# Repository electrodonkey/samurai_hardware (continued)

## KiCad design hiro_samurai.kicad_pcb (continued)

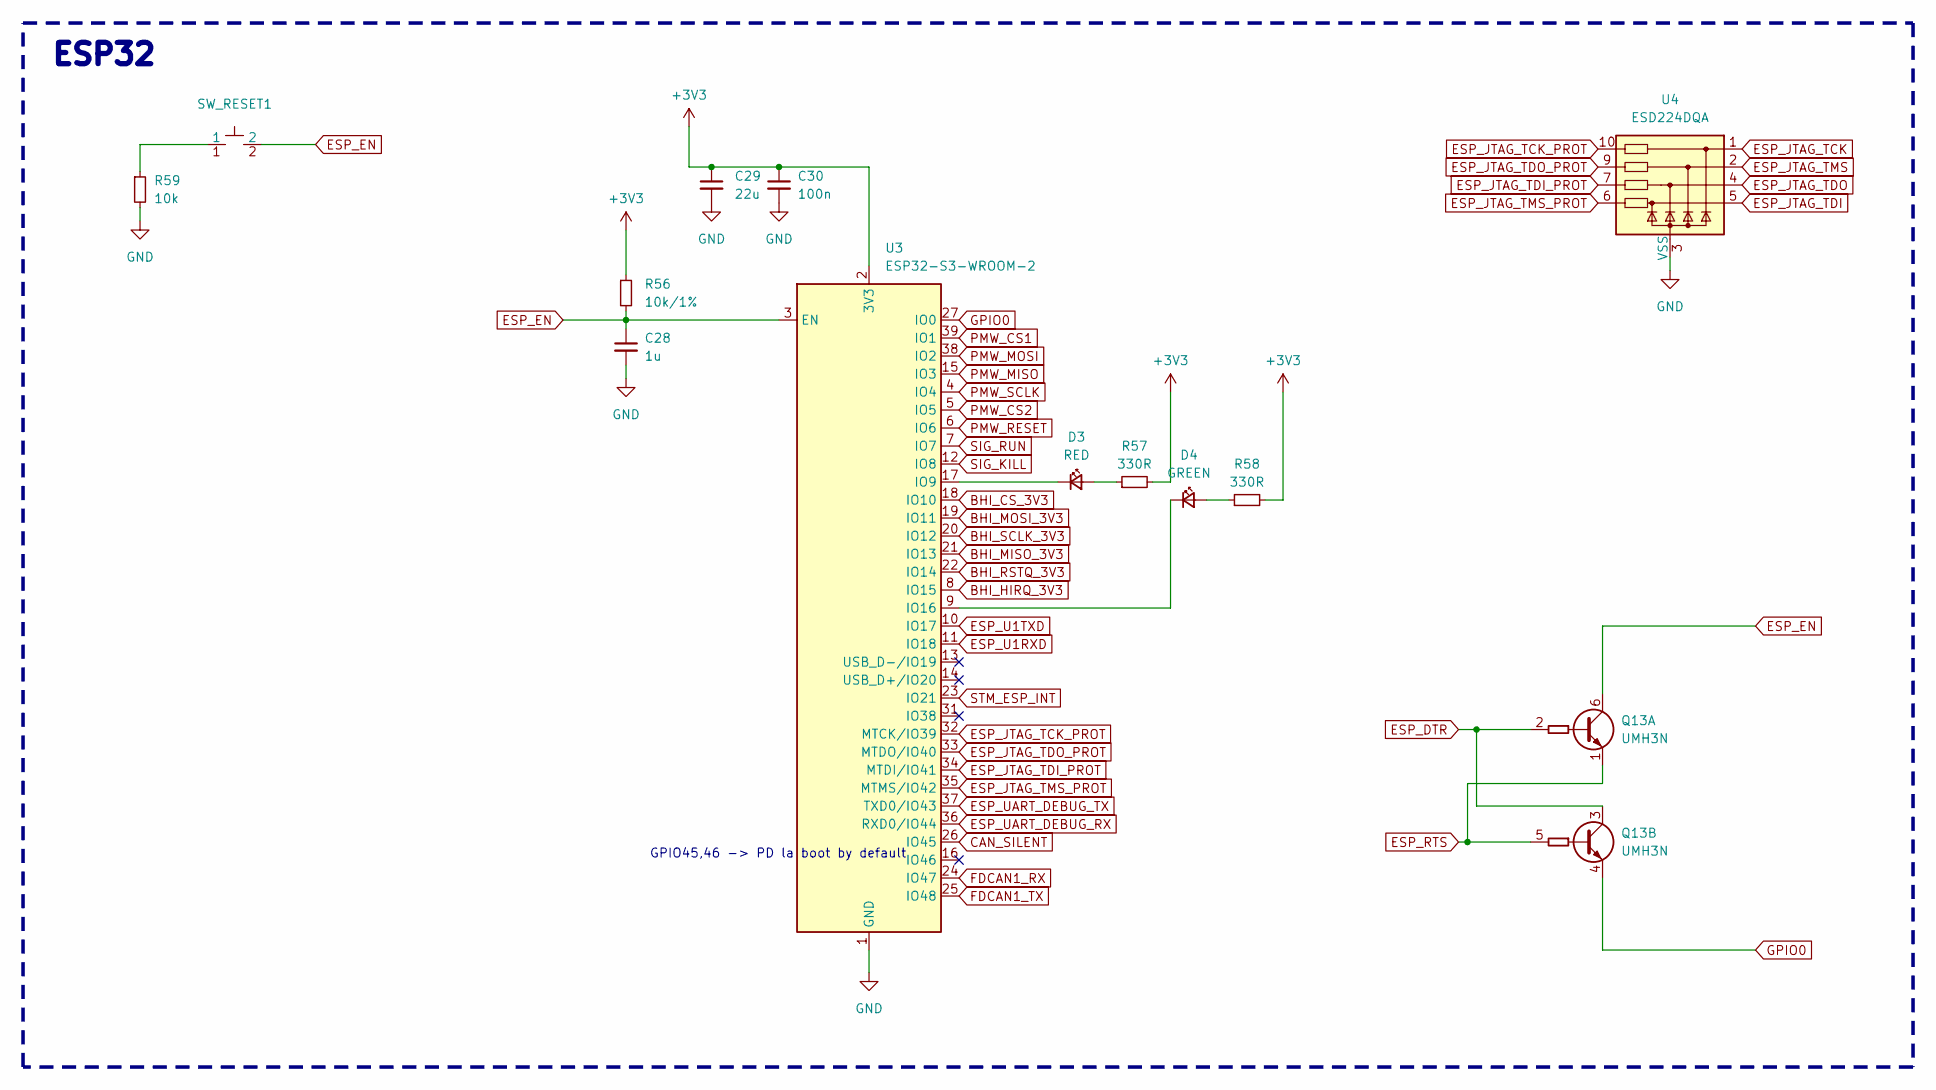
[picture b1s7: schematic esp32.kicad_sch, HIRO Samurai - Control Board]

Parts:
C28: 1u; C_0402_1005Metric_Pad0.74x0.62mm_HandSolder
C29: 22u; C_0603_1608Metric_Pad1.08x0.95mm_HandSolder
C30: 100n; C_0402_1005Metric_Pad0.74x0.62mm_HandSolder
D3: RED; LED_0603_1608Metric_Pad1.05x0.95mm_HandSolder
D4: GREEN; LED_0603_1608Metric_Pad1.05x0.95mm_HandSolder
Q13: UMH3N; SOT-363_SC-70-6
R56: 10k/1%; R_0402_1005Metric_Pad0.72x0.64mm_HandSolder
R57, R58: 330R; R_0402_1005Metric_Pad0.72x0.64mm_HandSolder
R59: 10k; R_0402_1005Metric_Pad0.72x0.64mm_HandSolder
SW_RESET1: TL1017AABF160QG
U3: ESP32-S3-WROOM-2
U4: ESD224DQA; Diodes_UDFN-10_1.0x2.5mm_P0.5mm

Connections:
+3V3: C29.1, C30.1, R56.1, R57.2, R58.2, U3.2 (3V3); also elsewhere on the board
BHI_CS_3V3: U3.18 (IO10); also elsewhere on the board
BHI_HIRQ_3V3: U3.8 (IO15); also elsewhere on the board
BHI_MISO_3V3: U3.21 (IO13); also elsewhere on the board
BHI_MOSI_3V3: U3.19 (IO11); also elsewhere on the board
BHI_RSTQ_3V3: U3.22 (IO14); also elsewhere on the board
BHI_SCLK_3V3: U3.20 (IO12); also elsewhere on the board
CAN_SILENT: U3.26 (IO45); also elsewhere on the board
ESP_DTR: Q13.2 (B1), Q13.3 (C2); also elsewhere on the board
ESP_EN: C28.1, Q13.6 (C1), R56.2, SW_RESET1.2, U3.3 (EN); also elsewhere on the board
ESP_JTAG_TCK: U4.1; also elsewhere on the board
ESP_JTAG_TCK_PROT: U3.32 (MTCK/IO39), U4.10
ESP_JTAG_TDI: U4.5; also elsewhere on the board
ESP_JTAG_TDI_PROT: U3.34 (MTDI/IO41), U4.7
ESP_JTAG_TDO: U4.4; also elsewhere on the board
ESP_JTAG_TDO_PROT: U3.33 (MTDO/IO40), U4.9
ESP_JTAG_TMS: U4.2; also elsewhere on the board
ESP_JTAG_TMS_PROT: U3.35 (MTMS/IO42), U4.6
ESP_RTS: Q13.1 (E1), Q13.5 (B2); also elsewhere on the board
ESP_U1RXD: U3.11 (IO18); also elsewhere on the board
ESP_U1TXD: U3.10 (IO17); also elsewhere on the board
ESP_UART_DEBUG_RX: U3.36 (RXD0/IO44); also elsewhere on the board
ESP_UART_DEBUG_TX: U3.37 (TXD0/IO43); also elsewhere on the board
FDCAN1_RX: U3.24 (IO47); also elsewhere on the board
FDCAN1_TX: U3.25 (IO48); also elsewhere on the board
GND: C28.2, C29.2, C30.2, R59.2, U3.1 (GND), U3.40 (GND), U3.41 (GND), U4.3 (VSS), U4.8 (VSS); also elsewhere on the board
GPIO0: Q13.4 (E2), U3.27 (IO0)
unnamed: D3.2 (A), R57.1
unnamed: D3.1 (K), U3.17 (IO9)
unnamed: D4.2 (A), R58.1
unnamed: D4.1 (K), U3.9 (IO16)
unnamed: R59.1, SW_RESET1.1
PMW_CS1: U3.39 (IO1); also elsewhere on the board
PMW_CS2: U3.5 (IO5); also elsewhere on the board
PMW_MISO: U3.15 (IO3); also elsewhere on the board
PMW_MOSI: U3.38 (IO2); also elsewhere on the board
PMW_RESET: U3.6 (IO6); also elsewhere on the board
PMW_SCLK: U3.4 (IO4); also elsewhere on the board
SIG_KILL: U3.12 (IO8); also elsewhere on the board
SIG_RUN: U3.7 (IO7); also elsewhere on the board
STM_ESP_INT: U3.23 (IO21); also elsewhere on the board

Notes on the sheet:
GPIO45,46 -> PD la boot by default
ESP32

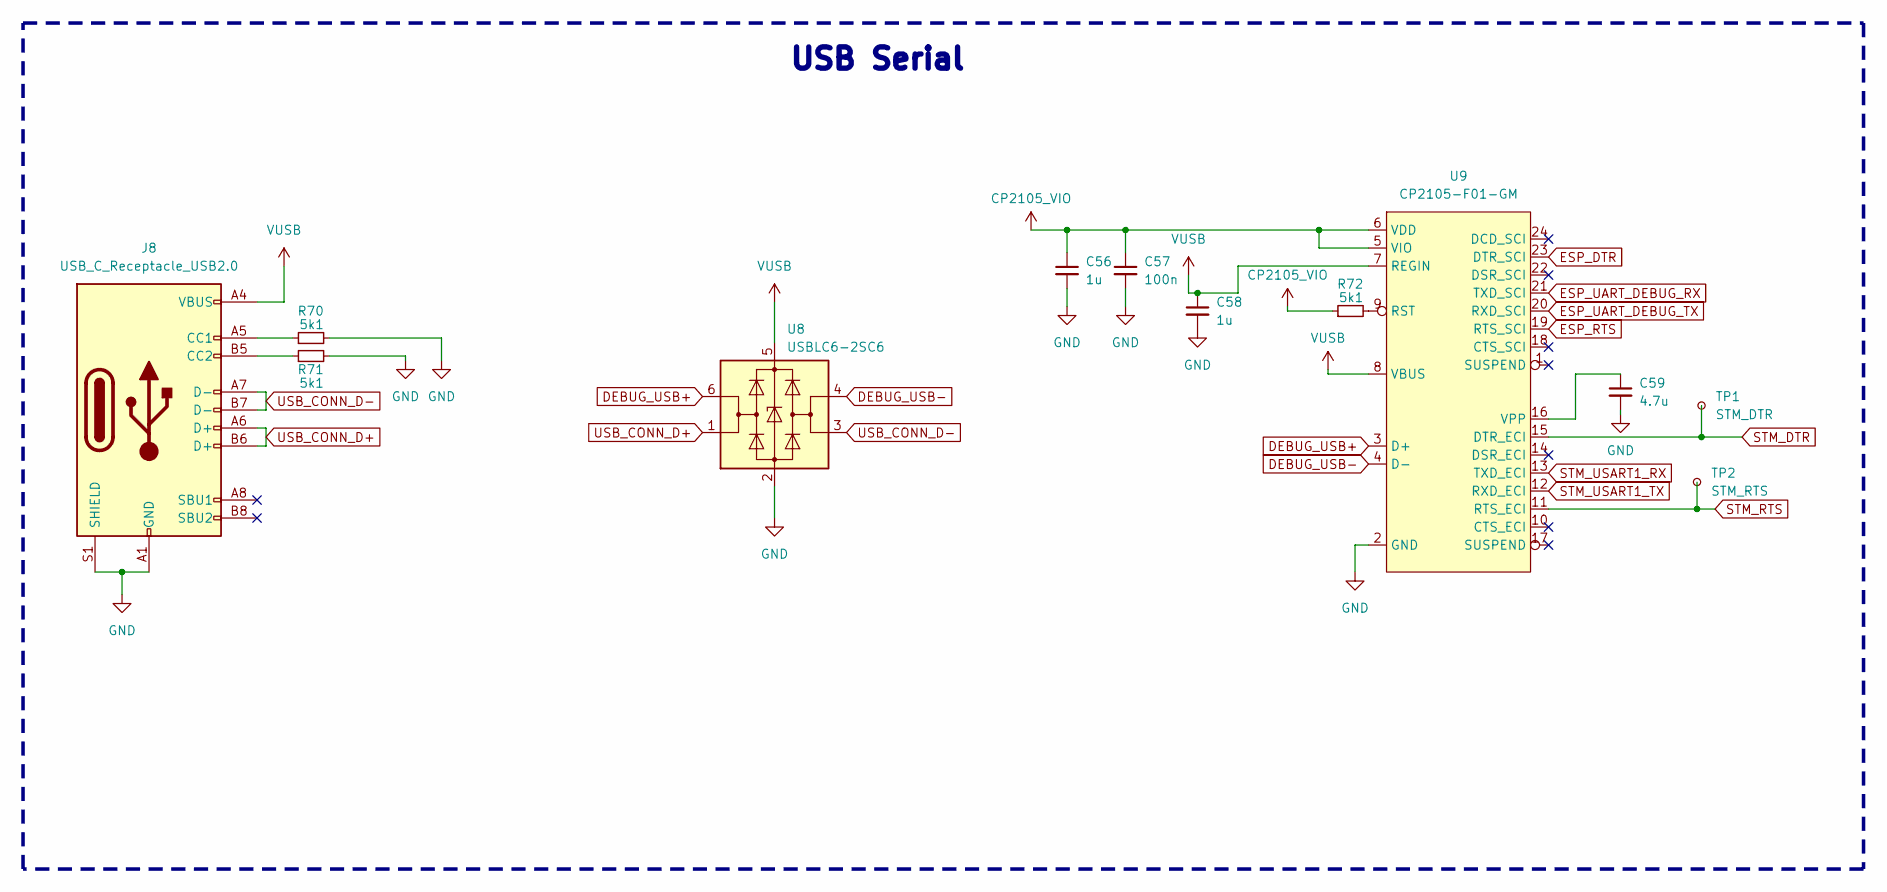
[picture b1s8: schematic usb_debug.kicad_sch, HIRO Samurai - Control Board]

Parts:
C56, C58: 1u; C_0402_1005Metric_Pad0.74x0.62mm_HandSolder
C57: 100n; C_0402_1005Metric_Pad0.74x0.62mm_HandSolder
C59: 4.7u; C_0402_1005Metric_Pad0.74x0.62mm_HandSolder
J8: USB_C_Receptacle_USB2.0; USB_C_Receptacle_GCT_USB4115-03-C
R70, R71, R72: 5k1; R_0402_1005Metric_Pad0.72x0.64mm_HandSolder
TP1: STM_DTR; TestPoint_Pad_D1.0mm
TP2: STM_RTS; TestPoint_Pad_D1.0mm
U8: USBLC6-2SC6; SOT-23-6
U9: CP2105-F01-GM; QFN-24-1EP_4x4mm_P0.5mm_EP2.7x2.7mm

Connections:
CP2105_VIO: C56.1, C57.1, R72.1, U9.5 (VIO), U9.6 (VDD)
DEBUG_USB+: U8.6 (I/O1), U9.3 (D+)
DEBUG_USB-: U8.4 (I/O2), U9.4 (D-)
ESP_DTR: U9.23 (DTR_SCI); also elsewhere on the board
ESP_RTS: U9.19 (RTS_SCI); also elsewhere on the board
ESP_UART_DEBUG_RX: U9.21 (TXD_SCI); also elsewhere on the board
ESP_UART_DEBUG_TX: U9.20 (RXD_SCI); also elsewhere on the board
GND: C56.2, C57.2, C58.2, C59.2, J8.A1 (GND), J8.A12 (GND), J8.B1 (GND), J8.B12 (GND), J8.S1 (SHIELD), R70.2, R71.2, U8.2 (GND), U9.2 (GND); also elsewhere on the board
unnamed: J8.A5 (CC1), R70.1
unnamed: J8.B5 (CC2), R71.1
unnamed: R72.2, U9.9 (RST)
unnamed: C59.1, U9.16 (VPP)
STM_DTR: TP1.1, U9.15 (DTR_ECI)
STM_RTS: TP2.1, U9.11 (RTS_ECI)
STM_USART1_RX: U9.13 (TXD_ECI); also elsewhere on the board
STM_USART1_TX: U9.12 (RXD_ECI); also elsewhere on the board
USB_CONN_D+: J8.A6 (D+), J8.B6 (D+), U8.1 (I/O1)
USB_CONN_D-: J8.A7 (D-), J8.B7 (D-), U8.3 (I/O2)
VUSB: C58.1, J8.A4 (VBUS), J8.A9 (VBUS), J8.B4 (VBUS), J8.B9 (VBUS), U8.5 (VBUS), U9.7 (REGIN), U9.8 (VBUS)

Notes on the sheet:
USB Serial

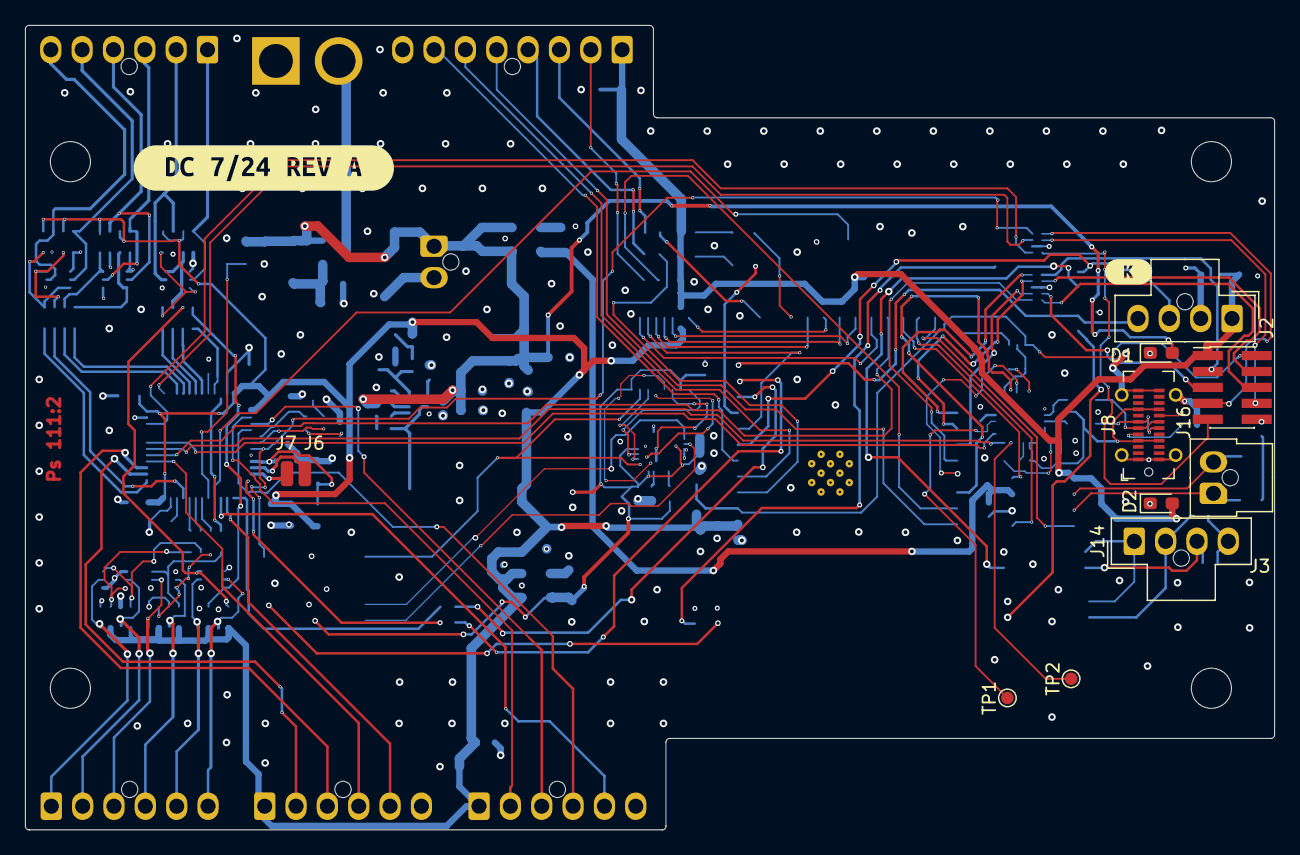
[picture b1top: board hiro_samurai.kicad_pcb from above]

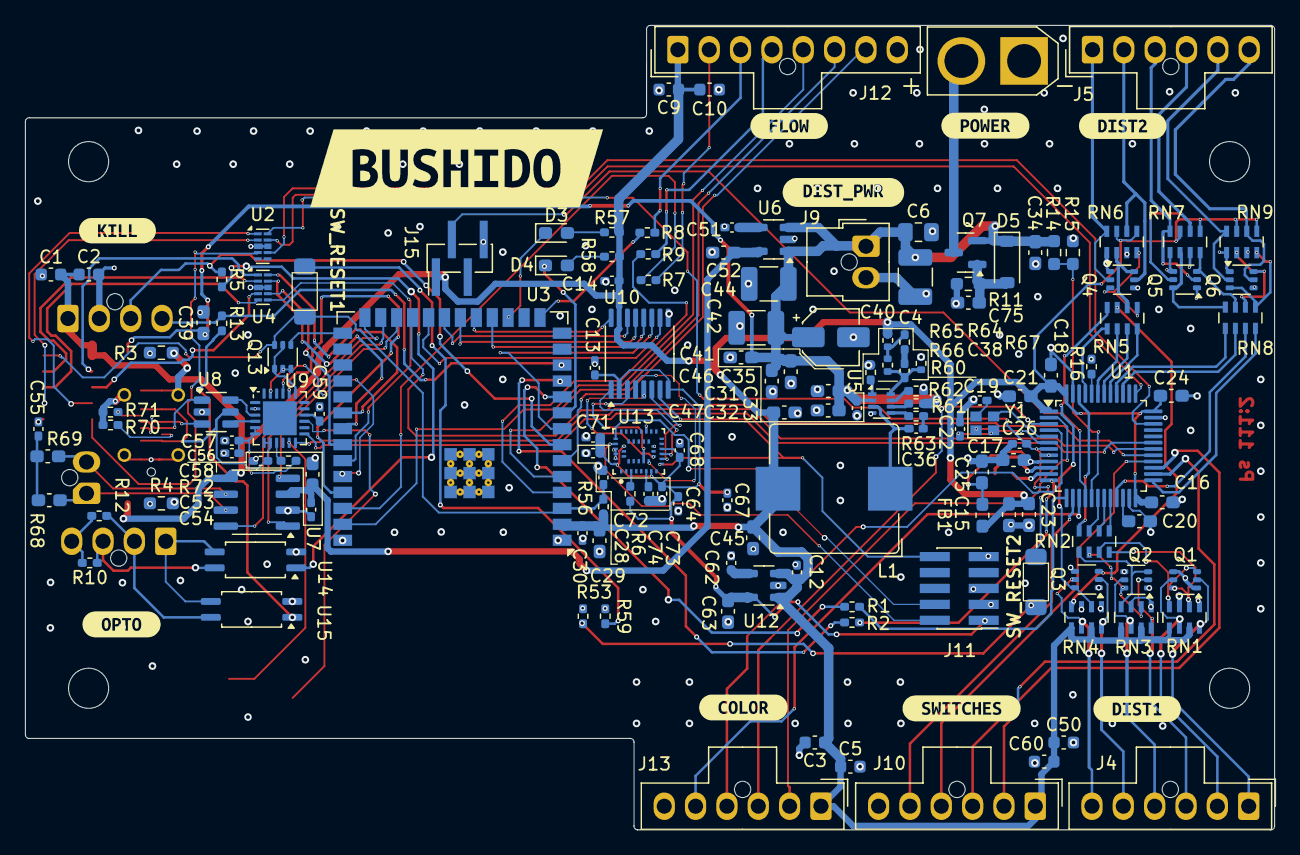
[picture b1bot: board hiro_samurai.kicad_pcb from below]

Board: 4 copper layers, 99.6 x 64.2 mm, 171 parts (154 on the bottom side), 159 nets.

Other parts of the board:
kibuzzard-66A557E3: G***; kibuzzard-66A557E3
kibuzzard-66A558AF: G***; kibuzzard-66A558AF
kibuzzard-66A558D5: G***; kibuzzard-66A558D5
kibuzzard-66A5583A: G***; kibuzzard-66A5583A
kibuzzard-66A5585D: G***; kibuzzard-66A5585D
kibuzzard-66A5588A: G***; kibuzzard-66A5588A
kibuzzard-66A55516: G***; kibuzzard-66A55516
kibuzzard-66A55816: G***; kibuzzard-66A55816
kibuzzard-66A55828: G***; kibuzzard-66A55828
kibuzzard-66A55877: G***; kibuzzard-66A55877
kibuzzard-66A55897: G***; kibuzzard-66A55897
kibuzzard-66A68797: G***; kibuzzard-66A68797

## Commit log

2024-07-03 First commit. Schematic done, layout in progress 10%
2024-07-25 Add files via upload
    Uploaded 3D directory
2024-07-25 Added finished hiro_sumo_pretty
2024-07-28 Routing done by @Turlinahi
2024-07-28 Add render of board
